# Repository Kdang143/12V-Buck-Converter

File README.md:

# 12V-Buck-Converter
•	Created a buck converter for Ryerson’s Robotics Club Rover to reduce input voltages of 12-volts to 5-volts output.

•	Utilized datasheets, Eagle Autodesk, and MultiSIM to design an appropriate switch regulator with >80% efficiency.

**Listed Components**

• 1x 100uF Capacitor to deal with input transient voltage noise.

• 1x 1000uF Capacitor to deal with output voltage noise and loop stability

• 1x 100uH Inductor for continous mode operation

• 1x Zener diode to provide a return path for the inductor current when switcher is off

• 1x LM2576-ADJ to allow a adjustabled feedback loop to control the voltage output

**Schematic**

**Board**

**Final Product**

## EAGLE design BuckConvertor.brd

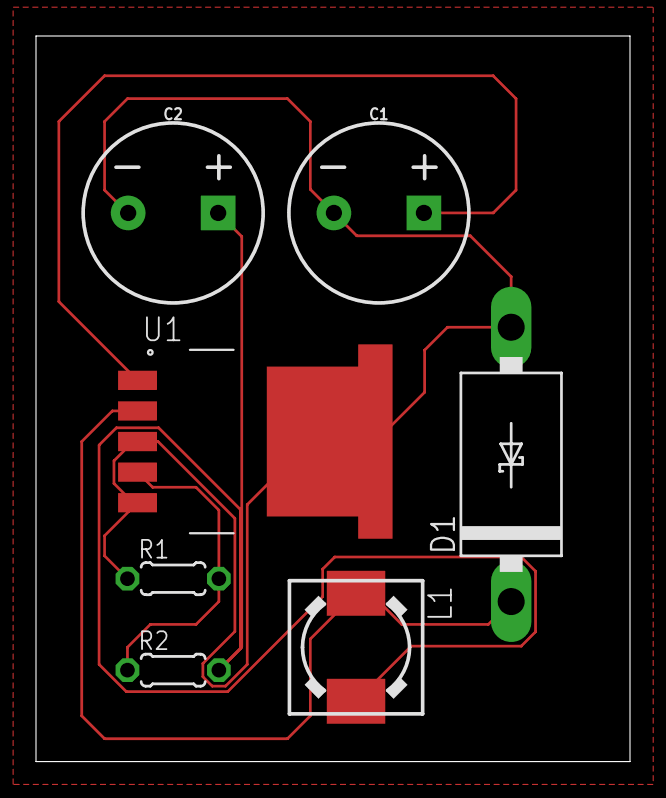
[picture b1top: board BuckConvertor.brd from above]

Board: 2 copper layers, 33.0 x 40.3 mm, 7 parts (0 on the bottom side), 5 nets.

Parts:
C1: 100uF; CPOL-RADIAL-5MM-10MM
C2: 1000uF; CPOL-RADIAL-5MM-10MM
D1: MBR360G; DIOB_MBR360G
L1: 100uH; DR73
R1: 2k; 0204/5
R2: 6.12k; 0204/5
U1: LM2576HVS-ADJ/NOPB; REG_LM2576HVS-ADJ/NOPB

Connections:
GND: C1.-, C2.-, D1.A, R1.1, U1.3, U1.5, U1.6, U1.7
unnamed: D1.C, L1.1, U1.2
unnamed: R1.2, R2.1, U1.4
VIN: C1.+, U1.1
VOUT: C2.+, L1.2, R2.2

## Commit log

2021-01-08 Create Schematic and Board

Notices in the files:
parts and their libraries:
SparkFun-Capacitors: Licensing: Creative Commons ShareAlike 4.0 International - https://creativecommons.org/licenses/by-sa/4.0
